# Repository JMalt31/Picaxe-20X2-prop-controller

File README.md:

# Picaxe-20X2-prop-controller
This is a prop or robot controller based on the picaxe 20X2 Microcontroller. 
This PCB was created with kiCad 6.0
I find this system much easier to use then the Arduino. I also have not found anything that the Arduino can do that this controller cannot do. 
The Picaxe get a bad rap for being a quote "less powerful or beginner Micocontroller" when that is simply not the case. 
There is also a Picaxe board that has the Arduino form factor and can use Arduino shields. 
If I need something that the Picaxe cannot handle then I will use the ESP32 controller which can also be programmed in Python.

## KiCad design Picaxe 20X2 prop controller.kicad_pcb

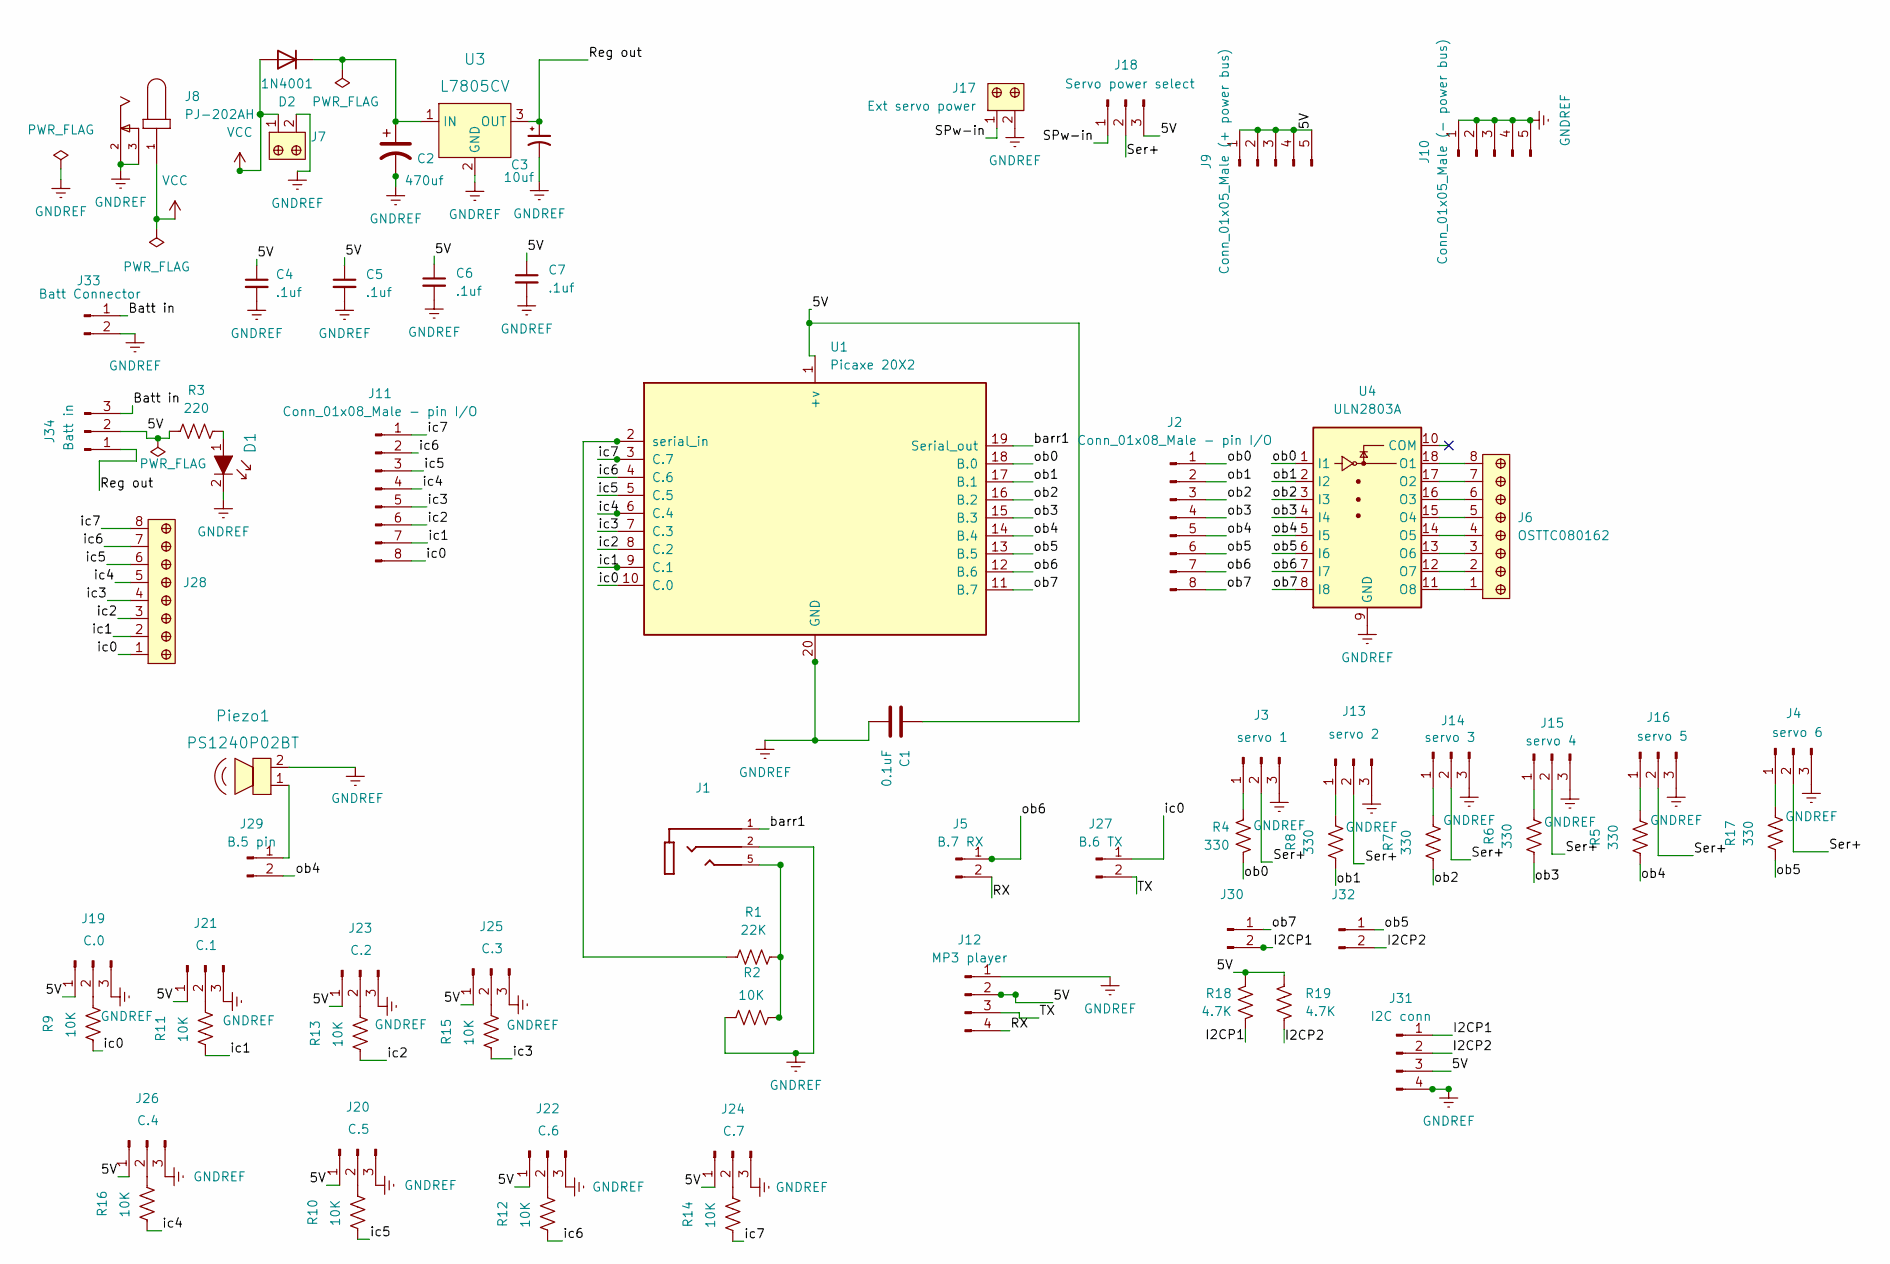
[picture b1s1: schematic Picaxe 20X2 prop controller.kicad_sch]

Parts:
C1: 0.1uF; C_Disc_D5.0mm_W2.5mm_P5.00mm
C2: 470uf; CP_Radial_D10.0mm_P5.00mm
C3: 10uf; CP_Radial_D5.0mm_P2.50mm
C4, C5, C6, C7: .1uf; C_Disc_D3.0mm_W2.0mm_P2.50mm
D1: LTL2R3KEK; LED_5mm_Radial; MPN LTL2R3KEK; Digi-Key_PN 160-1682-ND
D2: 1N4001; D_DO-41_SOD81_P10.16mm_Horizontal
J1: FC68131; CLIFF_FC68131; PARTREV 5
J2, J11: Conn_01x08_Male - pin I/O; PinHeader_1x08_P2.54mm_Vertical
J3: servo 1; PinHeader_1x03_P2.54mm_Vertical
J4: servo 6; PinHeader_1x03_P2.54mm_Vertical
J5: B.7 RX; PinHeader_1x02_P2.54mm_Vertical
J6, J28: OSTTC080162; Term_Block_1x8_P5mm; MPN OSTTC080162; Digi-Key_PN ED2606-ND
J7: OSTTC020162; Term_Block_1x2_P5mm; MPN OSTTC020162; Digi-Key_PN ED2600-ND
J8: PJ-202AH; CUI_PJ-202AH; PART_REV 1.02
J9: Conn_01x05_Male (+ power bus); PinHeader_1x05_P2.54mm_Vertical
J10: Conn_01x05_Male (- power bus); PinHeader_1x05_P2.54mm_Vertical
J12: MP3 player; Catalex MP3 player board
J13: servo 2; PinHeader_1x03_P2.54mm_Vertical
J14: servo 3; PinHeader_1x03_P2.54mm_Vertical
J15: servo 4; PinHeader_1x03_P2.54mm_Vertical
J16: servo 5; PinHeader_1x03_P2.54mm_Vertical
J17: Ext servo power; Term_Block_1x2_P5mm; MPN OSTTC020162; Digi-Key_PN ED2600-ND
J18: Servo power select; PinHeader_1x03_P2.54mm_Vertical
J19: C.0; PinHeader_1x03_P2.54mm_Vertical
J20: C.5; PinHeader_1x03_P2.54mm_Vertical
J21: C.1; PinHeader_1x03_P2.54mm_Vertical
J22: C.6; PinHeader_1x03_P2.54mm_Vertical
J23: C.2; PinHeader_1x03_P2.54mm_Vertical
J24: C.7; PinHeader_1x03_P2.54mm_Vertical
J25: C.3; PinHeader_1x03_P2.54mm_Vertical
J26: C.4; PinHeader_1x03_P2.54mm_Vertical
J27: B.6 TX; PinHeader_1x02_P2.54mm_Vertical
J29: B.5 pin; PinHeader_1x02_P2.54mm_Vertical
J30: B.7; PinHeader_1x02_P2.54mm_Vertical
J31: I2C conn; PinHeader_1x04_P2.54mm_Vertical
J32: B.5; PinHeader_1x02_P2.54mm_Vertical
J33: Batt Connector; PinHeader_1x02_P2.54mm_Vertical
J34: Batt in; PinHeader_1x03_P2.54mm_Vertical
Piezo1: PS1240P02BT; Piezo_Transducer_THT_PS1240P02BT; MPN PS1240P02BT; Digi-Key_PN 445-2525-1-ND
R1: 22K; R_Axial_DIN0207_L6.3mm_D2.5mm_P10.16mm_Horizontal
R2, R9, R10, R11, R12, R13, R14, R15, R16: 10K; R_Axial_DIN0207_L6.3mm_D2.5mm_P10.16mm_Horizontal
R3: 220; R_Axial_DIN0207_L6.3mm_D2.5mm_P10.16mm_Horizontal
R4, R5, R6, R7, R8, R17: 330; R_Axial_DIN0207_L6.3mm_D2.5mm_P10.16mm_Horizontal
R18, R19: 4.7K; R_Axial_DIN0207_L6.3mm_D2.5mm_P10.16mm_Horizontal
U1: Picaxe 20X2; DIP-20_W7.62mm_LongPads
U3: L7805CV; TO-220-3; MPN L7805CV; Digi-Key_PN 497-1443-5-ND
U4: ULN2803A; DIP-18_W7.62mm_LongPads

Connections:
/5V: C1.1, C4.1, C5.1, C6.1, C7.1, J9.1, J9.2, J9.3, J9.4, J9.5, J12.2, J18.3, J19.1, J20.1, J21.1, J22.1, J23.1, J24.1, J25.1, J26.1, J31.3, J34.2, R3.2, R18.2, R19.1, U1.1 (+v)
/Batt in: J33.1, J34.3
/I2CP1: J30.2, J31.1, R18.1
/I2CP2: J31.2, J32.2, R19.2
/RX: J5.2, J12.4
/Reg out: C3.1, J34.1, U3.3 (OUT)
/SPw-in: J17.1, J18.1
/Ser+: J3.2, J4.2, J13.2, J14.2, J15.2, J16.2, J18.2
/TX: J12.3, J27.2
/barr1: J1.1, U1.19 (Serial_out)
/ic0: J11.8, J27.1, J28.1, R9.2, U1.10 (C.0)
/ic1: J11.7, J28.2, R11.2, U1.9 (C.1)
/ic2: J11.6, J28.3, R13.2, U1.8 (C.2)
/ic3: J11.5, J28.4, R15.2, U1.7 (C.3)
/ic4: J11.4, J28.5, R16.2, U1.6 (C.4)
/ic5: J11.3, J28.6, R10.2, U1.5 (C.5)
/ic6: J11.2, J28.7, R12.2, U1.4 (C.6)
/ic7: J11.1, J28.8, R14.2, U1.3 (C.7)
/ob0: J2.1, R4.1, U1.18 (B.0), U4.1 (I1)
/ob1: J2.2, R8.2, U1.17 (B.1), U4.2 (I2)
/ob2: J2.3, R7.2, U1.16 (B.2), U4.3 (I3)
/ob3: J2.4, R6.2, U1.15 (B.3), U4.4 (I4)
/ob4: J2.5, J29.2, R5.2, U1.14 (B.4), U4.5 (I5)
/ob5: J2.6, J32.1, R17.2, U1.13 (B.5), U4.6 (I6)
/ob6: J2.7, J5.1, U1.12 (B.6), U4.7 (I7)
/ob7: J2.8, J30.1, U1.11 (B.7), U4.8 (I8)
GNDREF: C1.2, C2.2, C3.2, C4.2, C5.2, C6.2, C7.2, D1.2, J1.2, J3.3, J4.3, J7.2, J8.2, J8.3, J10.1, J10.2, J10.3, J10.4, J10.5, J12.1, J13.3, J14.3, J15.3, J16.3, J17.2, J19.3, J20.3, J21.3, J22.3, J23.3, J24.3, J25.3, J26.3, J31.4, J33.2, Piezo1.2, R2.2, U1.20 (GND), U3.2 (GND), U4.9 (GND)
unnamed: C2.1, D2.1 (K), U3.1 (IN)
unnamed: D1.1, R3.1
unnamed: J1.5, R1.1, R2.1
unnamed: J3.1, R4.2
unnamed: J4.1, R17.1
unnamed: J6.1, U4.11 (O8)
unnamed: J6.2, U4.12 (O7)
unnamed: J6.3, U4.13 (O6)
unnamed: J6.4, U4.14 (O5)
unnamed: J6.5, U4.15 (O4)
unnamed: J6.6, U4.16 (O3)
unnamed: J6.7, U4.17 (O2)
unnamed: J6.8, U4.18 (O1)
unnamed: J13.1, R8.1
unnamed: J14.1, R7.1
unnamed: J15.1, R6.1
unnamed: J16.1, R5.1
unnamed: J19.2, R9.1
unnamed: J20.2, R10.1
unnamed: J21.2, R11.1
unnamed: J22.2, R12.1
unnamed: J23.2, R13.1
unnamed: J24.2, R14.1
unnamed: J25.2, R15.1
unnamed: J26.2, R16.1
unnamed: J29.1, Piezo1.1
unnamed: R1.2, U1.2 (serial_in)
VCC: D2.2 (A), J7.1, J8.1

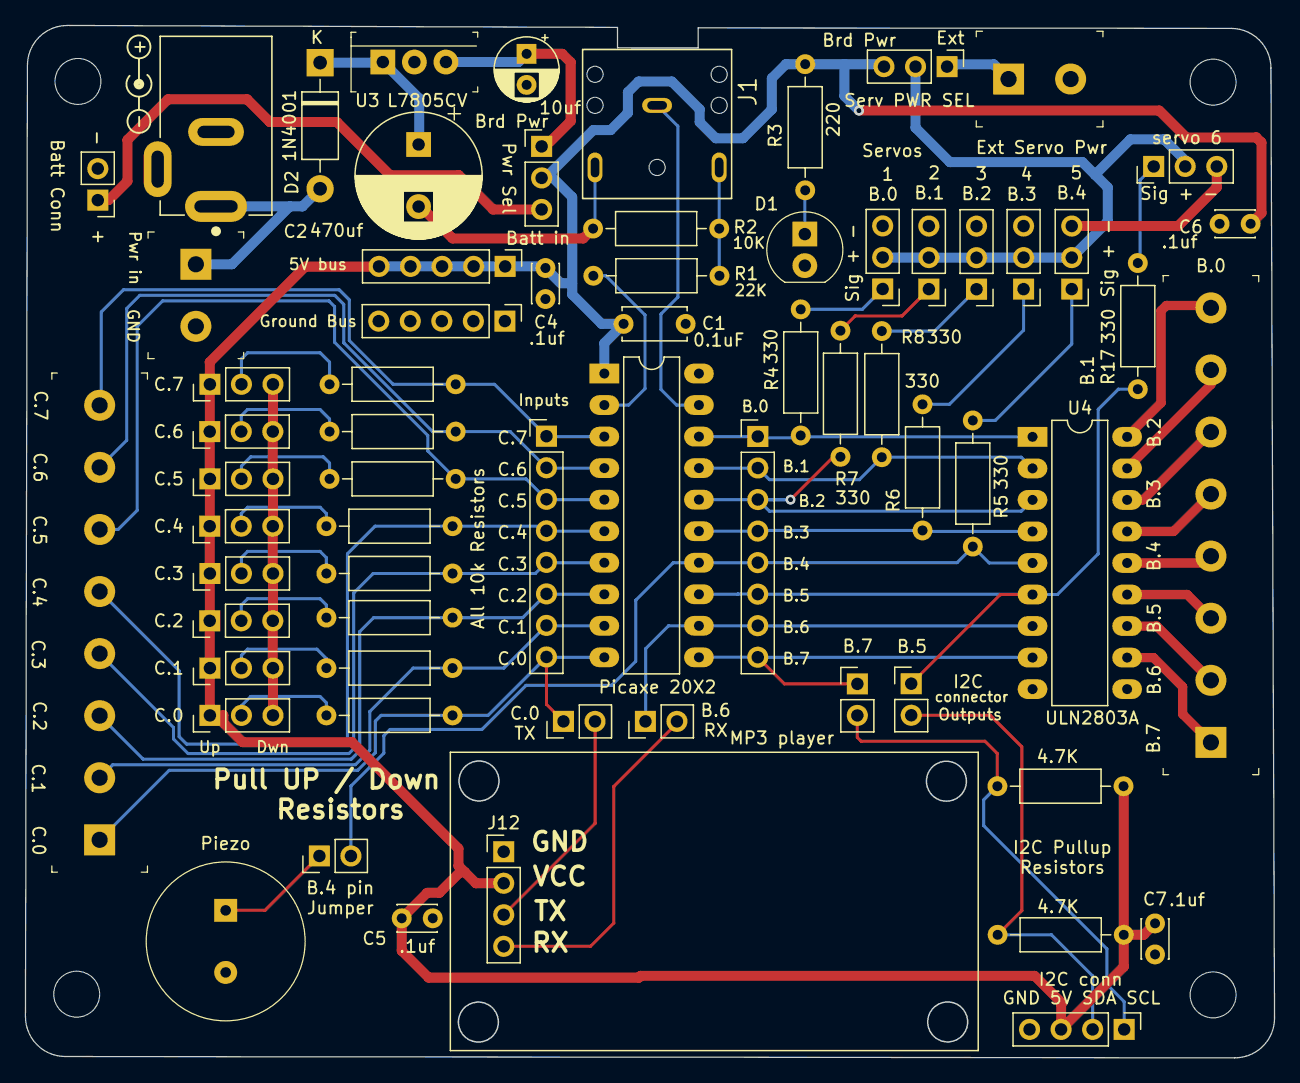
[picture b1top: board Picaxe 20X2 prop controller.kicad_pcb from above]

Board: 2 copper layers, 100.6 x 83.1 mm, 66 parts (0 on the bottom side), 55 nets.

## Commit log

2022-12-17 my first commit
2022-12-18 added the 8 pin terminal block to the inputs
2022-12-18 added a piezo and b.5 select jumper
2022-12-18 forgot to save the schematic file after added the peizo and jumper
2022-12-18 test of git diff
2022-12-31 Move 20X2 to Git
    Will branch to see about moving the I2C connector
2022-12-31 Create README.md
    Added the read me file
2022-12-31 Moved I2C connector and started to add a battery select
    Created a branch to move the I2C connector
2023-01-01 Moved I2c connector and added battery select option
    Added a battery connector and a select jumper to switch between the onboard regulator and the battery input connector. I also moved the I2C connector and added jumpers to disconnect the pins if neede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
2023-01-02 Added battery input polarity and changed 10uF to 2.4mm pin spacing
2023-01-02 Board complete Beta test 1
